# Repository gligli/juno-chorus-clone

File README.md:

juno-chorus-clone
=================

Roland Juno-60 chorus board clone

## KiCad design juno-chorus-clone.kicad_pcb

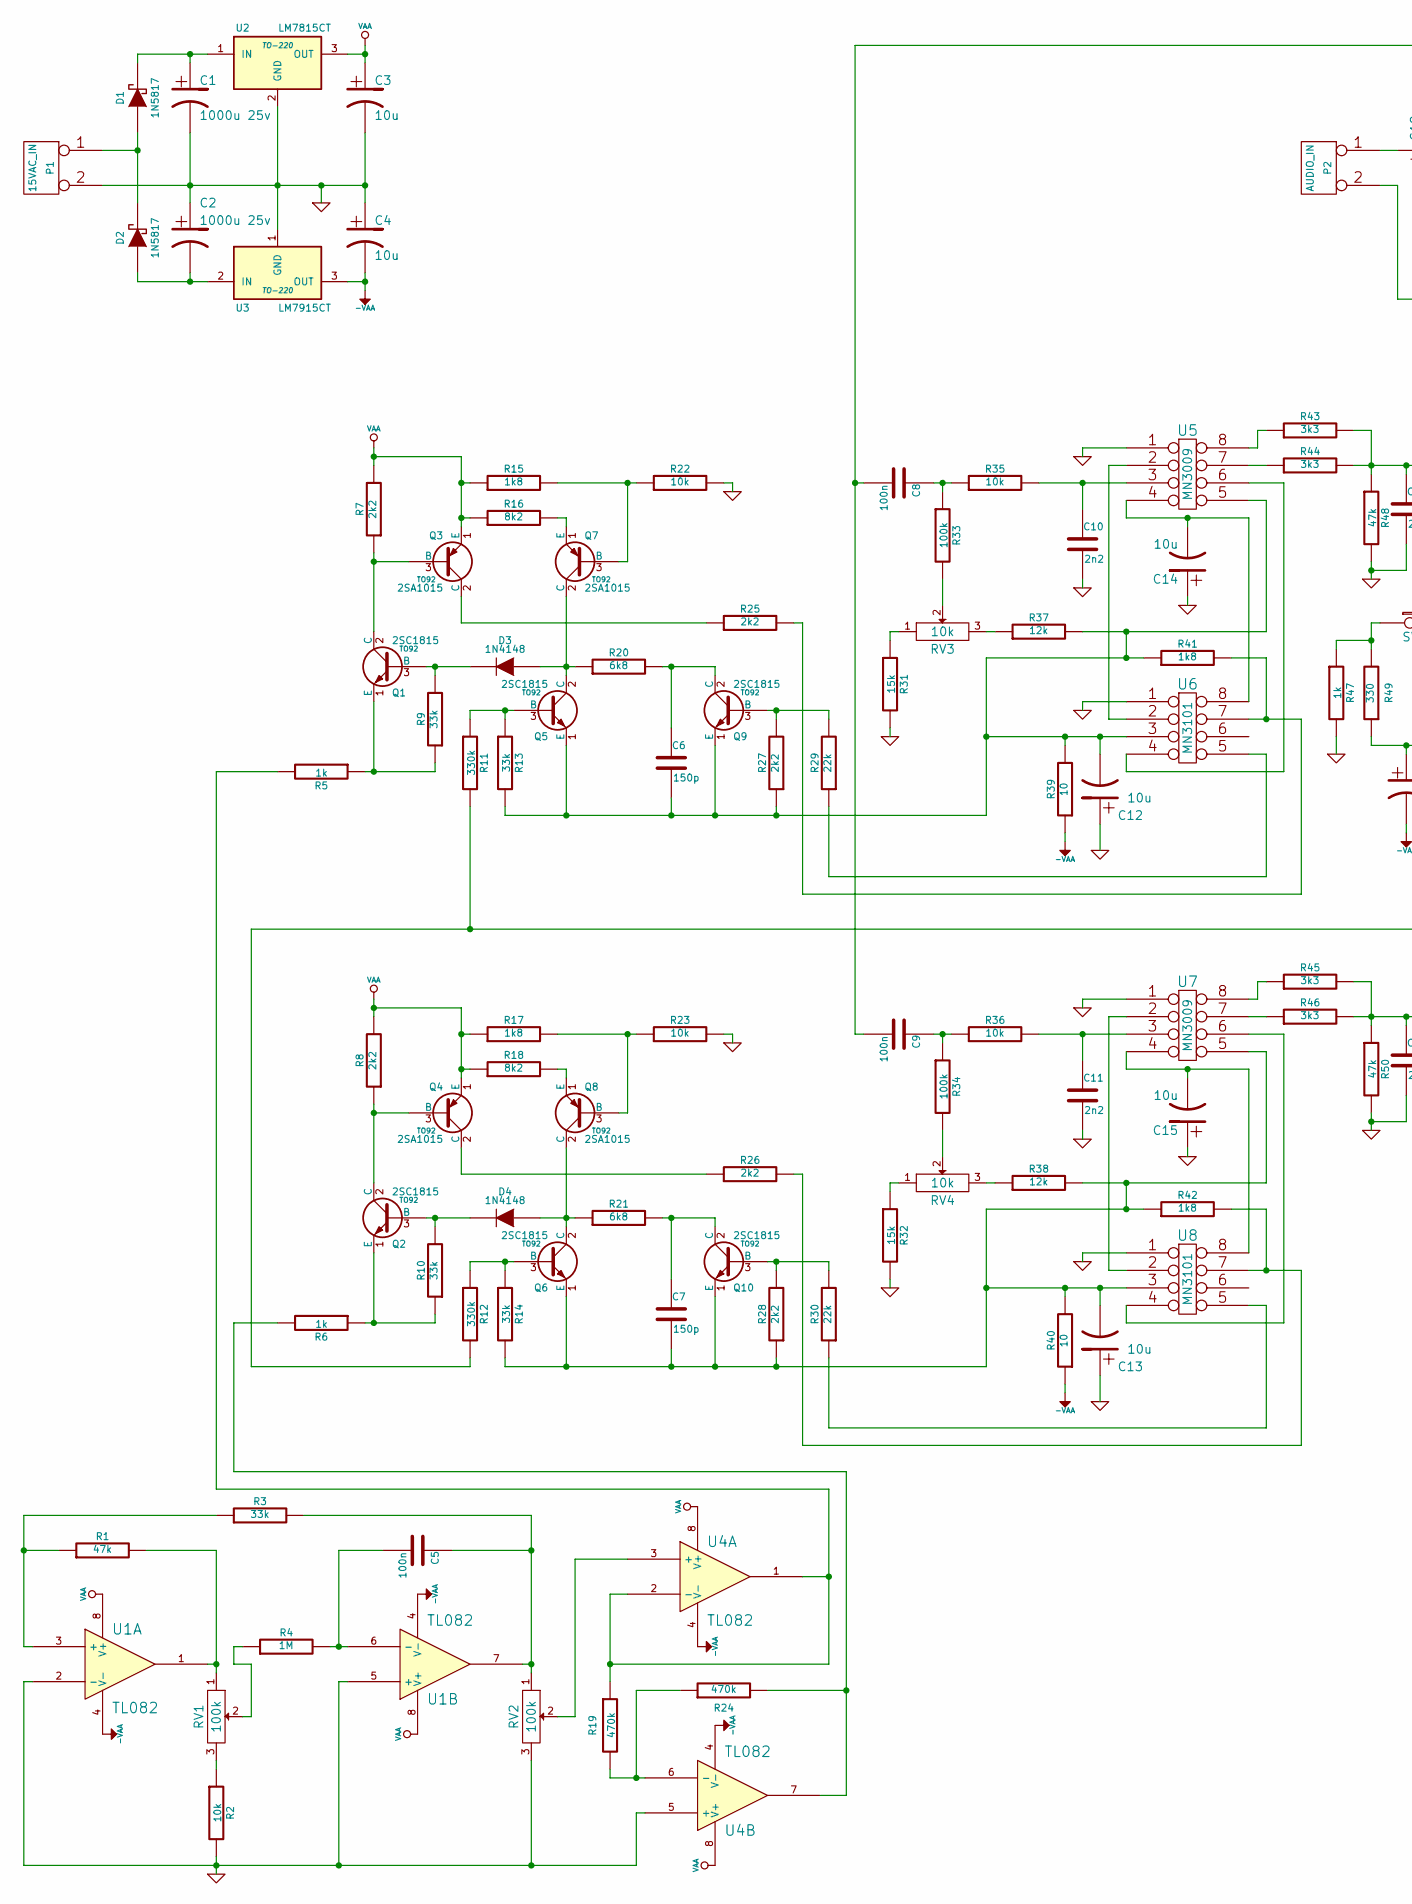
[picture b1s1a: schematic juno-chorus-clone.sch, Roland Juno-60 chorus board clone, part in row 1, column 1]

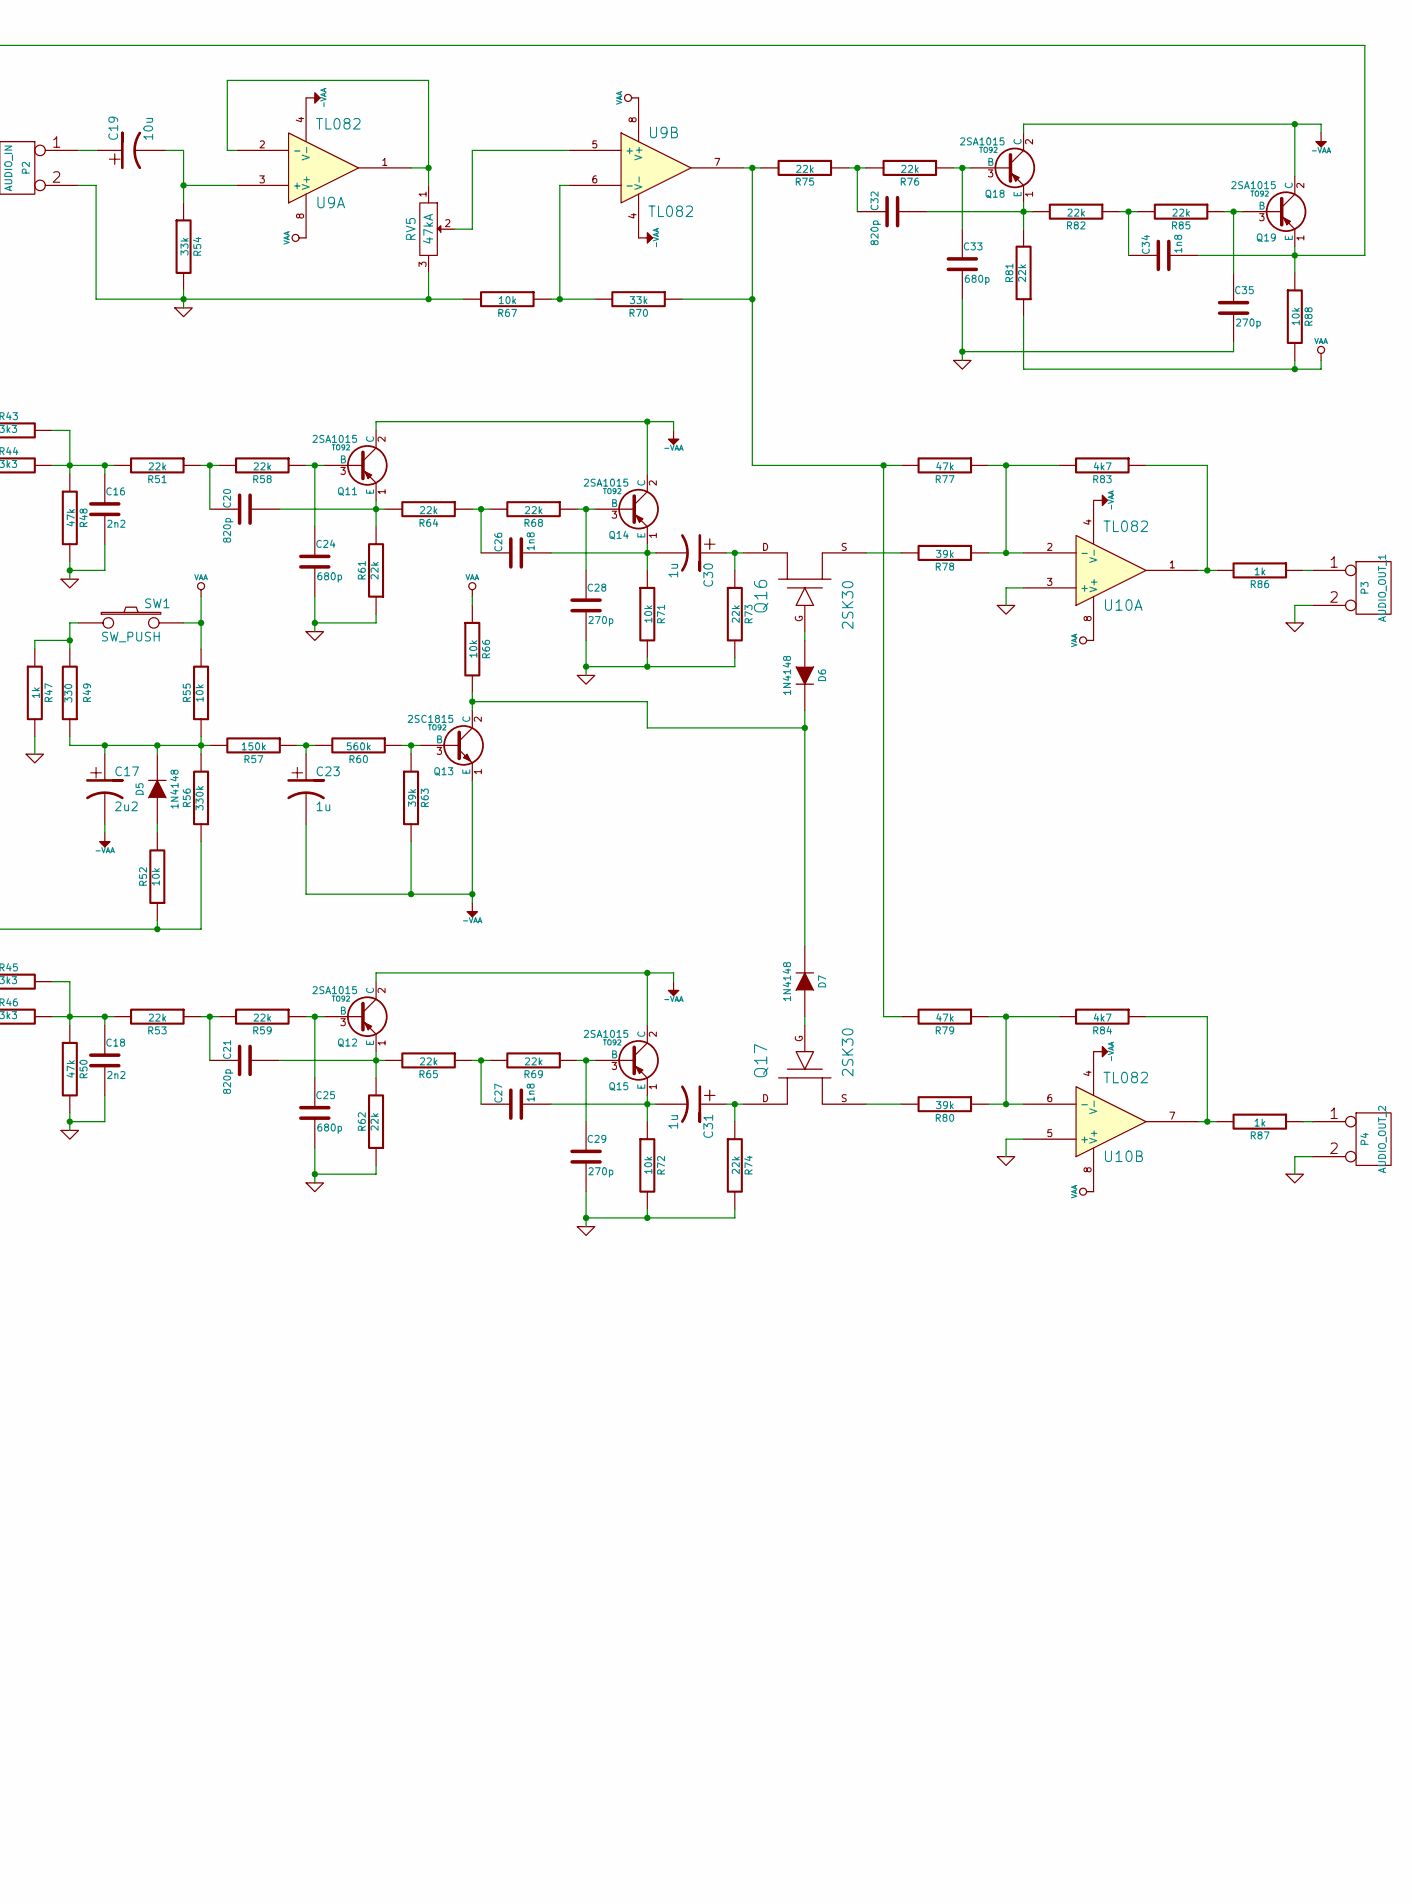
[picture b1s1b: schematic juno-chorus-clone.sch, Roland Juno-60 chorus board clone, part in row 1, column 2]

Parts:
C1, C2: 1000u 25v
C3, C4, C12, C13, C14, C15, C19: 10u
C5, C8, C9: 100n
C6, C7: 150p
C10, C11, C16, C18: 2n2
C17: 2u2
C20, C21, C32: 820p
C23, C30, C31: 1u
C24, C25, C33: 680p
C26, C27, C34: 1n8
C28, C29, C35: 270p
D1, D2: 1N5817
D3, D4, D5, D6, D7: 1N4148
P1: 15VAC_IN
P2: AUDIO_IN
P3: AUDIO_OUT_1
P4: AUDIO_OUT_2
Q1, Q2, Q5, Q6, Q9, Q10, Q13: 2SC1815; TO92
Q3, Q4, Q7, Q8, Q11, Q12, Q14, Q15, Q18, Q19: 2SA1015; TO92
Q16, Q17: 2SK30
R1, R48, R50, R77, R79: 47k
R2, R22, R23, R35, R36, R52, R55, R66, R67, R71, R72, R88: 10k
R3, R9, R10, R13, R14, R54, R70: 33k
R4: 1M
R5, R6, R47, R86, R87: 1k
R7, R8, R25, R26, R27, R28: 2k2
R11, R12, R56: 330k
R15, R17, R41, R42: 1k8
R16, R18: 8k2
R19, R24: 470k
R20, R21: 6k8
R29, R30, R51, R53, R58, R59, R61, R62, R64, R65, R68, R69, R73, R74, R75, R76, R81, R82, R85: 22k
R31, R32: 15k
R33, R34: 100k
R37, R38: 12k
R39, R40: 10
R43, R44, R45, R46: 3k3
R49: 330
R57: 150k
R60: 560k
R63, R78, R80: 39k
R83, R84: 4k7
RV1, RV2: 100k
RV3, RV4: 10k
RV5: 47kA
SW1: SW_PUSH
U1, U4, U9, U10: TL082
U2: LM7815CT; TO-220
U3: LM7915CT; TO-220
U5, U7: MN3009
U6, U8: MN3101

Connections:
-VAA: C4.2, C17.2, C23.2, Q11.2 (C), Q12.2 (C), Q13.1 (E), Q14.2 (C), Q15.2 (C), Q18.2 (C), Q19.2 (C), R39.1, R40.1, R63.2, U1.4 (V-), U3.3 (OUT), U4.4 (V-), U9.4 (V-), U10.4 (V-)
GND: C1.2, C2.1, C3.2, C4.1, C10.2, C11.2, C12.1, C13.1, C14.1, C15.1, C16.2, C18.2, C24.2, C25.2, C28.2, C29.2, C33.2, C35.2, P1.2 (PM), P2.2 (PM), P3.2 (PM), P4.2 (PM), R2.2, R22.2, R23.2, R31.2, R32.2, R47.2, R48.2, R50.2, R54.2, R61.1, R62.1, R67.2, R71.2, R72.2, R73.2, R74.2, RV2.3, RV5.3, U1.2 (-), U1.5 (+), U2.2 (GND), U3.1 (GND), U4.5 (+), U5.1, U6.1, U7.1, U8.1, U10.3 (+), U10.5 (+)
unnamed: U5.2, U6.2
unnamed: R37.1, RV3.3
unnamed: R25.2, R41.2, U6.7
unnamed: C6.1, Q9.2 (C), R20.2
unnamed: Q5.3 (B), R11.1, R13.1
unnamed: R31.1, RV3.1
unnamed: R29.1, U6.5
unnamed: Q7.3 (B), R15.2, R22.1
unnamed: Q9.3 (B), R27.2, R29.2
unnamed: Q7.1 (E), R16.2
unnamed: C6.2, C12.2, Q5.1 (E), Q9.1 (E), R13.2, R27.1, R37.2, R39.2, R41.1, U5.5, U6.3
unnamed: D3.2 (K), Q1.3 (B), R9.2
unnamed: Q3.2 (C), R25.1
unnamed: D3.1 (A), Q5.2 (C), Q7.2 (C), R20.1
unnamed: Q1.2 (C), Q3.3 (B), R7.1
unnamed: C27.1, R65.1, R69.2
unnamed: C29.1, Q15.3 (B), R69.1
unnamed: C27.2, C31.2, Q15.1 (E), R72.1
unnamed: C21.2, Q12.1 (E), R62.2, R65.2
unnamed: C21.1, R53.1, R59.2
unnamed: C31.1, Q17.D, R74.1
unnamed: R84.1, R87.2, U10.7
unnamed: C25.1, Q12.3 (B), R59.1
unnamed: Q1.1 (E), R5.1, R9.1
unnamed: R79.1, R80.1, R84.2, U10.6 (-)
unnamed: P4.1, R87.1
unnamed: C14.2, U5.4, U6.8
unnamed: P3.1, R86.1
unnamed: C33.1, Q18.3 (B), R76.1
unnamed: C20.1, R51.1, R58.2
unnamed: R83.1, R86.2, U10.1
unnamed: R77.1, R78.1, R83.2, U10.2 (-)
unnamed: C19.1, P2.1
unnamed: R70.1, R75.2, R77.2, R79.2, U9.7
unnamed: R67.1, R70.2, U9.6 (-)
unnamed: C32.1, R75.1, R76.2
unnamed: RV5.2, U9.5 (+)
unnamed: RV5.1, U9.1, U9.2 (-)
unnamed: C35.1, Q19.3 (B), R85.1
unnamed: C34.1, R82.1, R85.2
unnamed: C20.2, Q11.1 (E), R61.2, R64.2
unnamed: C32.2, Q18.1 (E), R81.2, R82.2
unnamed: C16.1, R43.2, R44.2, R48.1, R51.2
unnamed: R33.2, RV3.2
unnamed: R43.1, U5.8
unnamed: R44.1, U5.7
unnamed: C10.1, R35.2, U5.3
unnamed: U5.6, U6.4
unnamed: C8.1, R33.1, R35.1
unnamed: C24.1, Q11.3 (B), R58.1
unnamed: C26.1, R64.1, R68.2
unnamed: C28.1, Q14.3 (B), R68.1
unnamed: C26.2, C30.2, Q14.1 (E), R71.1
unnamed: C30.1, Q16.D, R73.1
unnamed: D6.1 (A), Q16.G
unnamed: Q16.S, R78.2
unnamed: Q17.S, R80.2
unnamed: D5.1 (A), R52.2
unnamed: R11.2, R12.2, R52.1, R56.1
unnamed: D6.2 (K), D7.2 (K), Q13.2 (C), R66.2
unnamed: R47.1, R49.2, SW1.1
unnamed: C8.2, C9.2, C34.2, Q19.1 (E), R88.1
unnamed: C23.1, R57.1, R60.2
unnamed: Q13.3 (B), R60.1, R63.1
unnamed: C17.1, D5.2 (K), R49.1, R55.1, R56.2, R57.2
unnamed: Q8.1 (E), R18.2
unnamed: Q4.2 (C), R26.1
unnamed: R6.2, R24.2, U4.7
unnamed: R19.2, R24.1, U4.6 (-)
unnamed: Q2.1 (E), R6.1, R10.1
unnamed: U7.6, U8.4
unnamed: D4.1 (A), Q6.2 (C), Q8.2 (C), R21.1
unnamed: Q2.2 (C), Q4.3 (B), R8.1
unnamed: C11.1, R36.2, U7.3
unnamed: R45.1, U7.8
unnamed: R46.1, U7.7
unnamed: R34.2, RV4.2
unnamed: C9.1, R34.1, R36.1
unnamed: D7.1 (A), Q17.G
unnamed: U7.2, U8.2
unnamed: D4.2 (K), Q2.3 (B), R10.2
unnamed: C18.1, R45.2, R46.2, R50.1, R53.2
unnamed: Q10.3 (B), R28.2, R30.2
unnamed: R26.2, R42.2, U8.7
unnamed: R32.1, RV4.1
unnamed: R30.1, U8.5
unnamed: Q8.3 (B), R17.2, R23.1
unnamed: RV2.2, U4.3 (+)
unnamed: C15.2, U7.4, U8.8
unnamed: C7.1, Q10.2 (C), R21.2
unnamed: Q6.3 (B), R12.1, R14.1
unnamed: R38.1, RV4.3
unnamed: C7.2, C13.2, Q6.1 (E), Q10.1 (E), R14.2, R28.1, R38.2, R40.2, R42.1, U7.5, U8.3
unnamed: R2.1, RV1.3
unnamed: C5.1, R3.2, RV2.1, U1.7
unnamed: R4.1, RV1.2
unnamed: C2.2, D2.1 (A), U3.2 (IN)
unnamed: D1.1 (A), D2.2 (K), P1.1
unnamed: R1.2, RV1.1, U1.1
unnamed: C1.1, D1.2 (K), U2.1 (IN)
unnamed: R5.2, R19.1, U4.1, U4.2 (-)
unnamed: C19.2, R54.1, U9.3 (+)
unnamed: C5.2, R4.2, U1.6 (-)
unnamed: R1.1, R3.1, U1.3 (+)
VAA: C3.1, Q3.1 (E), Q4.1 (E), R7.2, R8.2, R15.1, R16.1, R17.1, R18.1, R55.2, R66.1, R81.1, R88.2, SW1.2, U1.8 (V+), U2.3 (OUT), U4.8 (V+), U9.8 (V+), U10.8 (V+)

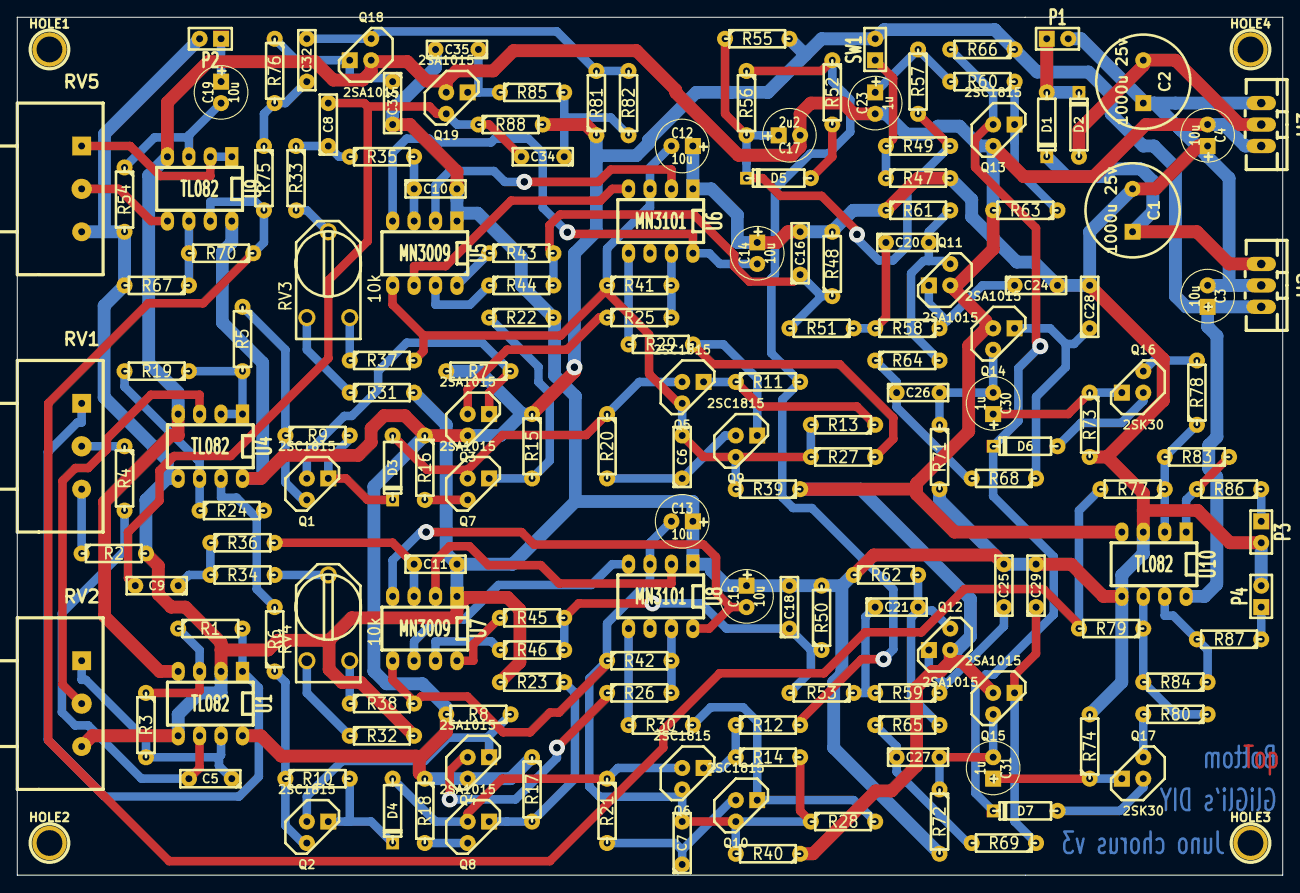
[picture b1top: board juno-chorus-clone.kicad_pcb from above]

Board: 2 copper layers, 149.9 x 101.6 mm, 172 parts (0 on the bottom side), 107 nets.

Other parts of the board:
HOLE1, HOLE2, HOLE3, HOLE4: P***; 1pin

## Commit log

2014-04-21 Adding kicad project and unverified schematics
2014-04-21 schematics fixes
2014-04-21 missing names
2014-04-21 fix transistors pinouts
2014-04-21 annotation
2014-04-21 adding netlist -- start of PCB
2014-04-21 start of PCB placement
2014-05-02 pcb placement
2014-05-02 PCB v1
2014-05-03 schematics: fixes to make it work (tested)
2014-05-04 pcb: v2 with post-debug fixes, should be ok to build
2014-05-04 sch: fixing wrong res values in BBDs output stages
2014-05-07 sch: output level / input gain pot fixes
2014-07-23 adding BOM
2015-09-12 1N5817 -> 1N5819 (1N5817 can't handle 15VAC)
